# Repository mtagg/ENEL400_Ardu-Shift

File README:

repository for circuit/ PCB files used in the design of a small, arduino-powered portable gaming device, using simple components and the "Arduboy" firmware library.
All PCB files created using KiCAD.

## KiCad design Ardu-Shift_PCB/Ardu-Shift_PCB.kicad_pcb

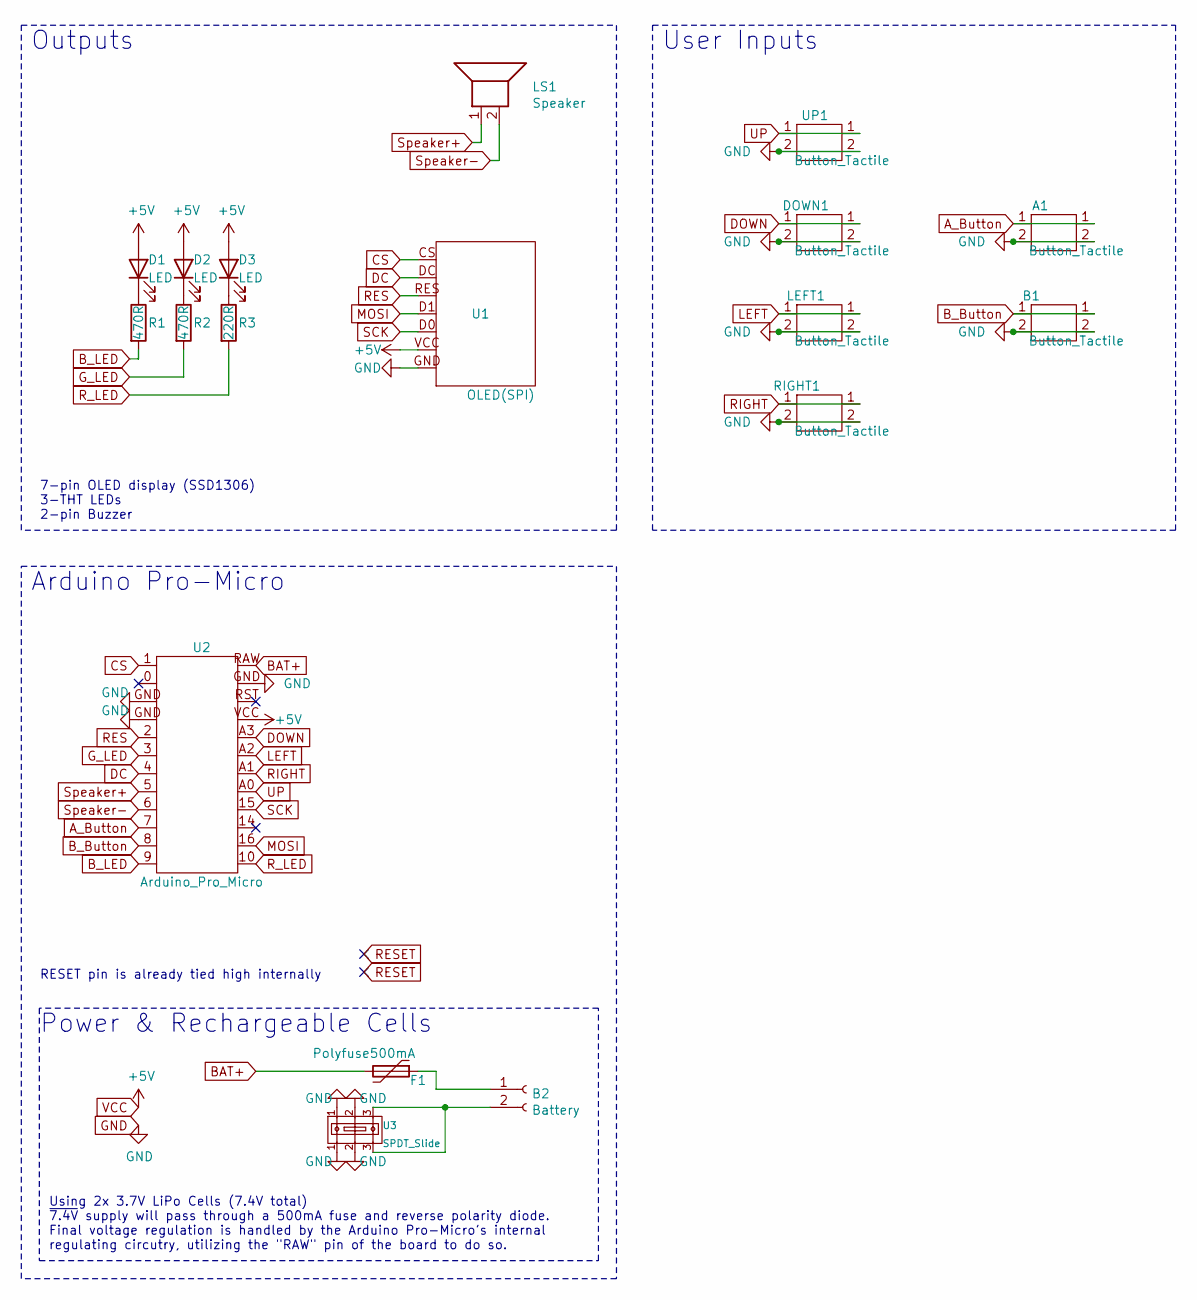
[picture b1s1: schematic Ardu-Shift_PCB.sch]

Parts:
A1: Button_Tactile; SW_PUSH_6mm_H4.3mm
B1: Button_Tactile; SW_PUSH_6mm_H4.3mm
B2: Battery; PinHeader_1x02_P2.54mm_Vertical
D1, D2, D3: LED; LED_D1.8mm_W3.3mm_H2.4mm
DOWN1: Button_Tactile; SW_PUSH_6mm_H4.3mm
F1: Polyfuse500mA; R_Axial_DIN0207_L6.3mm_D2.5mm_P7.62mm_Horizontal
LEFT1: Button_Tactile; SW_PUSH_6mm_H4.3mm
LS1: Speaker; Buzzer_12x9.5RM7.6
R1, R2: 470R; R_Axial_DIN0207_L6.3mm_D2.5mm_P7.62mm_Horizontal
R3: 220R; R_Axial_DIN0207_L6.3mm_D2.5mm_P7.62mm_Horizontal
RIGHT1: Button_Tactile; SW_PUSH_6mm_H4.3mm
U1: OLED(SPI); OLED(7pin)
U2: Arduino_Pro_Micro
U3: SPDT_Slide
UP1: Button_Tactile; SW_PUSH_6mm_H4.3mm

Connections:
A_Button: A1.1, U2.7
BAT+: F1.2, U2.RAW
B_Button: B1.1, U2.8
B_LED: R1.2, U2.9
CS: U1.CS, U2.1
DC: U1.DC, U2.4
DOWN: DOWN1.1, U2.A3
GND: A1.2, B1.2, DOWN1.2, LEFT1.2, RIGHT1.2, U1.GND, U2.GND, U3.1, U3.2, UP1.2
G_LED: R2.2, U2.3
LEFT: LEFT1.1, U2.A2
MOSI: U1.D1, U2.16
unnamed: B2.1, F1.1
unnamed: B2.2, U3.3
unnamed: D1.1 (K), R1.1
unnamed: D2.1 (K), R2.1
unnamed: D3.1 (K), R3.1
RES: U1.RES, U2.2
RIGHT: RIGHT1.1, U2.A1
R_LED: R3.2, U2.10
SCK: U1.D0, U2.15
Speaker+: LS1.1, U2.5
Speaker-: LS1.2, U2.6
UP: U2.A0, UP1.1
VCC: D1.2 (A), D2.2 (A), D3.2 (A), U1.VCC, U2.VCC

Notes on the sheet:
Arduino Pro-Micro
Outputs
User Inputs
Power & Rechargeable Cells
7-pin OLED display (SSD1306) 3-THT LEDs 2-pin Buzzer
RESET pin is already tied high internally
Using 2x 3.7V LiPo Cells (7.4V total) ~7.4V supply will pass through a 500mA fuse and reverse polarity diode. Final voltage regulation is handled by the Arduino Pro-Micro's internal regulating circutry, utilizing the "RAW" pin of the board to do so.

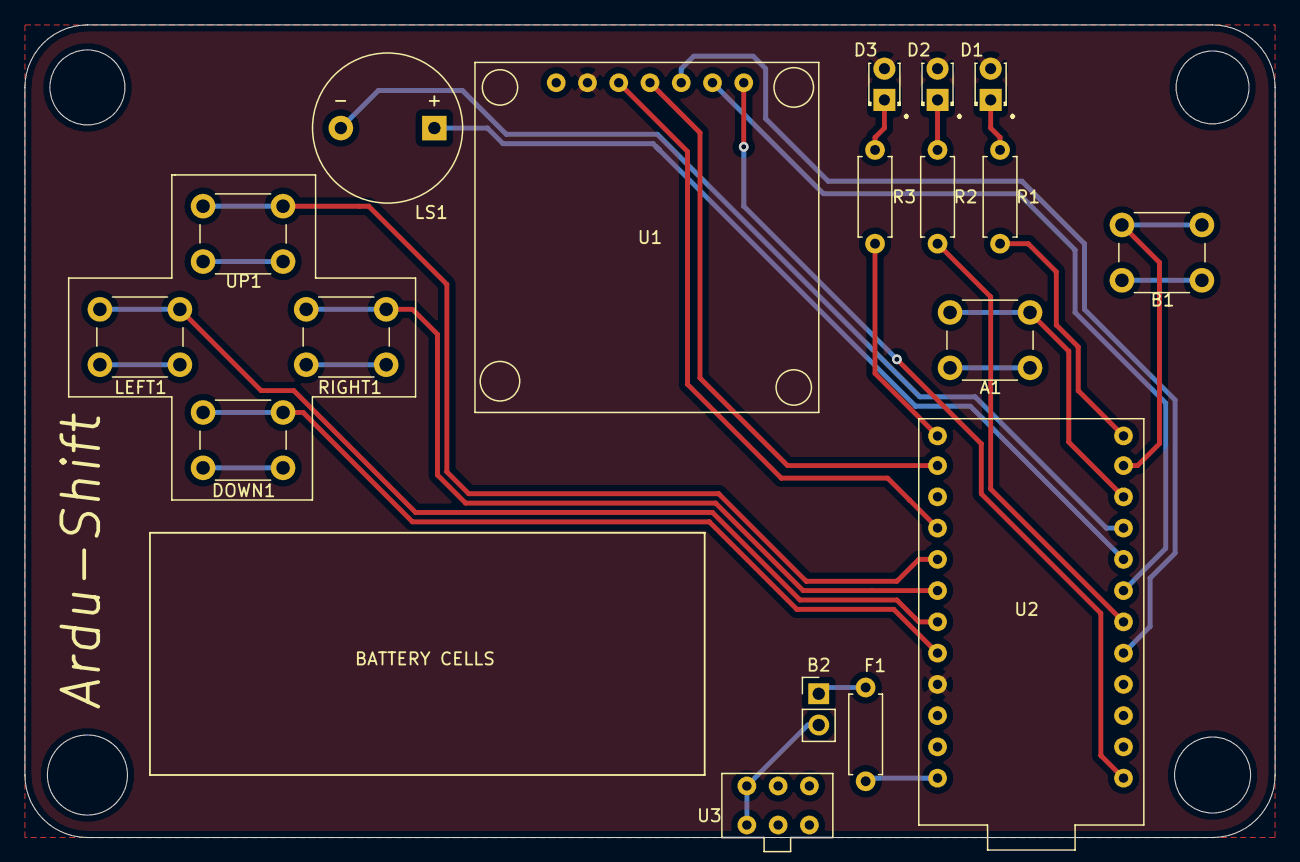
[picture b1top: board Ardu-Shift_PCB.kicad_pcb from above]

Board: 2 copper layers, 101.6 x 66.0 mm, 18 parts (0 on the bottom side), 24 nets.

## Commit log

2021-02-16 first commit, rought drafts/ incomplete schematic and pcb layout
2021-02-16 Create README
    added readme
2021-02-16 more 'realistic' adjustments to the location of electronics on the PCB
2021-02-16 first version of the final assembly/routing of game-device PCB
2021-02-16 added Ardu-shift branding to PCB on both silk layers
2021-02-17 added a power switch to ground for on/off functionality, added footprint for smaller speaker and updated all files.PDFs
2021-02-17 missed updating the circuit PDF on last commit
2021-02-17 swapped pins on schematic/PCB to work with arduboy library
2021-02-18 Updated PCB wiring, swapped some pins required for the 7-pin OLED to work with arduboy library
2021-02-19 finalized PCB design - ready for final review by team members. Gerber files generated for manufacturing
